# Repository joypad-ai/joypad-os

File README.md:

# Joypad OS

<p align="center">
  <picture>
    <source media="(prefers-color-scheme: dark)" srcset="docs/images/logo_solid.svg">
    <source media="(prefers-color-scheme: light)" srcset="docs/images/logo_solid_black.svg">
    
  </picture>
</p>
<p align="center">
  <strong>The Open-Source Firmware Platform for Game Controllers and Adapters</strong>
</p>
<p align="center">
  Build controller adapters, custom controllers, and assistive input devices — <br>on microcontrollers, not computers.
</p>
<p align="center">

</p>

---

## What is Joypad OS?

Joypad OS is firmware that runs on small microcontroller boards (RP2040, ESP32-S3, nRF52840) — the kind you'd find inside a controller or adapter, not on a PC. You flash it onto a chip and it handles everything: reading controllers, translating protocols, routing inputs to outputs, and managing button remapping.

**What you can build with it:**

- **Controller adapters** — Use any modern USB or Bluetooth controller on retro consoles (GameCube, Dreamcast, PCEngine, 3DO, and more) or convert retro controllers to USB
- **Custom controllers** — Wire up buttons, sticks, and sensors to a microcontroller and get a USB gamepad that works everywhere
- **Assistive gaming setups** — Merge multiple input devices (switches, joysticks, eye trackers) into a single controller output using flexible input routing
- **Wireless adapters** — Turn any Bluetooth controller into a wired USB gamepad for low-latency play

Under the hood, Joypad OS normalizes every input source into a common format, routes it through configurable player slots, and translates it into whatever output protocol the target needs — from retro console protocols bit-banged via PIO to modern USB HID and XInput.

Formerly known as **USBRetro**.

---

## I Have an Adapter — How Do I Update It?

1. **Download** the latest `.uf2` for your adapter from [Releases](https://github.com/joypad-ai/joypad-os/releases)
2. **Enter bootloader**: Hold BOOT + connect USB-C (or double-tap reset)
3. **Drag** the `.uf2` file onto the `RPI-RP2` drive that appears
4. **Done** — the drive ejects and your adapter is running the new firmware

**[Full installation guide](docs/getting-started/installation.md)** — troubleshooting, LED status codes, profile switching

---

## I Want to Build Something — Where Do I Start?

### Quick Start (RP2040)

```bash
# Install ARM toolchain (macOS)
brew install --cask gcc-arm-embedded cmake git

# Clone and initialize
git clone https://github.com/joypad-ai/joypad-os.git
cd joypad-os && make init

# Build an adapter
make usb2gc_kb2040     # USB/BT → GameCube
make usb2usb_feather   # USB/BT → USB HID
make bt2usb_pico_w     # Bluetooth → USB
make snes2usb_kb2040   # SNES controller → USB
```

### ESP32-S3

```bash
make init-esp                   # One-time ESP-IDF setup
make bt2usb_esp32s3             # Build
make flash-bt2usb_esp32s3       # Flash
```

### nRF52840

```bash
make init-nrf                               # One-time NCS setup
make bt2usb_seeed_xiao_nrf52840             # Build
make flash-bt2usb_seeed_xiao_nrf52840       # Flash
```

Output: `releases/joypad_os_<commit>_<app>_<board>.uf2`

**[Full build guide](docs/getting-started/building.md)** — prerequisites, all targets, ESP32/nRF setup, troubleshooting

---

## What Can It Do?

### Console Adapters

Use any USB or Bluetooth controller on retro consoles:

| Console | Apps | Highlights | Build | Docs |
|---------|------|-----------|-------|------|
| **PlayStation 4** | usb2usb | Local RSA auth, passthrough, rumble | [DIY](docs/hardware/diy.md) | [Guide](docs/architecture/ps4_auth.md) |
| **PCEngine / TurboGrafx-16** | usb2pce | Multitap (5 players), mouse, 2/3/6-button | [DIY](docs/hardware/diy.md) | [Guide](docs/apps/usb2pce.md) |
| **GameCube / Wii** | usb2gc, bt2gc | Profiles, rumble, keyboard mode | [Build](docs/hardware/builds/usb2gc.md) | [Guide](docs/apps/usb2gc.md) |
| **Sega Dreamcast** | usb2dc | Rumble, analog triggers, 4 players | [DIY](docs/hardware/diy.md) | [Guide](docs/apps/usb2dc.md) |
| **N64** | bt2n64 | Rumble pak emulation, profiles, BT | [DIY](docs/hardware/diy.md) | [Guide](docs/apps/bt2n64.md) |
| **Nuon DVD Players** | usb2nuon, bt2nuon | Controller, spinner (Tempest 3000), IGR | [DIY](docs/hardware/diy.md) | [Guide](docs/apps/usb2nuon.md) |
| **3DO Interactive Multiplayer** | usb23do | 8 players, mouse, extension passthrough | [DIY](docs/hardware/diy.md) | [Guide](docs/apps/usb23do.md) |
| **Neo Geo / SuperGun** | usb2neogeo | 7 profiles, 1L6B arcade layouts | [DIY](docs/hardware/diy.md) | [Guide](docs/apps/usb2neogeo.md) |
| **Casio Loopy** | usb2loopy | 4 players (experimental) | [DIY](docs/hardware/diy.md) | [Guide](docs/apps/usb2loopy.md) |

### USB & Wireless Adapters

| Adapter | What It Does | Platforms | Build | Docs |
|---------|-------------|-----------|-------|------|
| **USB2USB** | USB/BT controller → USB gamepad (XInput, PS3/4, Switch, etc.) | RP2040, nRF52840 | [DIY](docs/hardware/diy.md) | [Guide](docs/apps/usb2usb.md) |
| **BT2USB** | Bluetooth controller → wired USB gamepad | Pico W, ESP32-S3, nRF52840 | [Pico W](docs/hardware/builds/bt2usb-pico-w.md) | [Guide](docs/apps/bt2usb.md) |
| **WiFi2USB** | WiFi controller (JOCP) → USB gamepad | Pico W | [DIY](docs/hardware/diy.md) | [Guide](docs/apps/wifi2usb.md) |

### Native Controller Adapters

Convert retro controllers to USB or bridge them to other consoles:

| Adapter | From → To | Build | Docs |
|---------|----------|-------|------|
| **SNES2USB** | SNES/NES → USB | [KB2040](docs/hardware/builds/snes2usb-kb2040.md) | [Guide](docs/apps/snes2usb.md) |
| **NES2USB** | NES → USB | [DIY](docs/hardware/diy.md) | [Guide](docs/apps/nes2usb.md) |
| **N642USB** | N64 → USB | [DIY](docs/hardware/diy.md) | [Guide](docs/apps/n642usb.md) |
| **GC2USB** | GameCube → USB | [DIY](docs/hardware/diy.md) | [Guide](docs/apps/gc2usb.md) |
| **NEOGEO2USB** | Neo Geo arcade stick → USB | [DIY](docs/hardware/diy.md) | [Guide](docs/apps/neogeo2usb.md) |
| **LodgeNet2USB** | LodgeNet hotel controllers → USB | [Pico](docs/hardware/builds/lodgenet2usb-pico.md) | [Guide](docs/apps/lodgenet2usb.md) |
| **N642DC** | N64 → Dreamcast | [KB2040](docs/hardware/builds/n642dc-kb2040.md) | [Guide](docs/apps/n642dc.md) |
| **N642Nuon** | N64 → Nuon | [DIY](docs/hardware/diy.md) | [Guide](docs/apps/n642nuon.md) |
| **SNES23DO** | SNES → 3DO | [DIY](docs/hardware/diy.md) | [Guide](docs/apps/snes23do.md) |
| **LodgeNet2N64** | LodgeNet → N64 | [DIY](docs/hardware/diy.md) | [Guide](docs/apps/lodgenet2n64.md) |
| **LodgeNet2GC** | LodgeNet → GameCube | [DIY](docs/hardware/diy.md) | [Guide](docs/apps/lodgenet2gc.md) |

### Custom Controllers

Wire up GPIO buttons and analog sticks to build your own USB gamepad:

```bash
make controller_fisherprice_v1_kb2040  # Digital buttons → USB HID
make controller_fisherprice_v2_kb2040  # Buttons + analog stick → USB HID
make controller_macropad               # Adafruit MacroPad → USB HID
make universal_pico_w           # GPIO+JoyWing → BLE+USB HID (Pico W)
make universal_rp2040_abb       # GPIO+USB Host → USB HID (ABB Passthrough)
```

---

## Supported Input Devices

- **Xbox** — OG, 360, One, Series X|S (USB + Bluetooth)
- **PlayStation** — Classic, DS3, DS4, DualSense (USB + Bluetooth)
- **Nintendo** — Switch Pro, Switch 2 Pro, Joy-Con, NSO GameCube, GameCube adapter (USB + Bluetooth)
- **8BitDo** — PCE 2.4g, M30, NeoGeo, BT adapters
- **Other** — Hori, Logitech, Google Stadia, Sega Astro City, generic HID
- **Peripherals** — USB keyboards, mice, hubs, Bluetooth dongles
- **Native** — SNES, N64, GameCube, Neo Geo, LodgeNet hotel controllers (directly wired)

**[Full controller compatibility list](docs/hardware/controllers.md)**

---

## How It Works

```
Any Input                        Router                       Any Output
─────────                        ──────                       ──────────
USB controllers ──┐                                           ┌──→ Retro consoles
Bluetooth ────────┤                                           ├──→ USB gamepad
WiFi ─────────────┼──→  normalize  →  route  →  translate  ──┼──→ XInput / PS4 / Switch
SNES / N64 / GC ──┤         ↓                                ├──→ Keyboard + mouse
GPIO buttons ─────┘    profile_apply()                        └──→ Custom outputs
                    (button remapping)
```

- **Router** — SIMPLE (1:1), MERGE (all→one), or BROADCAST (all→all) modes
- **Profiles** — Per-app button remapping, cycled via SELECT + D-pad
- **Dual-Core** — Core 0 handles input, Core 1 handles timing-critical output (RP2040)
- **PIO** — Programmable I/O for console protocols (GameCube joybus, Dreamcast maple, etc.)

**[Architecture overview](docs/overview/architecture.md)** | **[Data flow](docs/overview/data-flow.md)**

---

## Platforms

| Platform | Chip | What Runs On It | Bluetooth | Build System |
|----------|------|----------------|-----------|--------------|
| **RP2040** | ARM Cortex-M0+ (dual-core) | All console adapters, USB output, custom controllers | Classic BT + BLE (Pico W) or via dongle | pico-sdk |
| **ESP32-S3** | Xtensa LX7 (dual-core) | bt2usb | BLE only | ESP-IDF |
| **nRF52840** | ARM Cortex-M4 | bt2usb, usb2usb | BLE only | nRF Connect SDK |

---

## Documentation

| Section | What's There |
|---------|-------------|
| **[Installation Guide](docs/getting-started/installation.md)** | Flashing firmware, troubleshooting, LED codes |
| **[Build Guide](docs/getting-started/building.md)** | Dev setup for macOS/Linux/Windows, all build targets |
| **[Supported Controllers](docs/hardware/controllers.md)** | USB, Bluetooth, keyboards, mice, dongles |
| **[Supported Boards](docs/hardware/boards.md)** | RP2040, ESP32-S3, nRF52840 board comparison |
| **[Wiring Guide](docs/hardware/wiring.md)** | USB host port + console connector pinouts |
| **[DIY Builds](docs/hardware/diy.md)** | Build your own, where to buy parts |
| **[ESP32-S3](docs/platforms/esp32.md)** | ESP-IDF setup, TinyUF2, architecture |
| **[nRF52840](docs/platforms/nrf52840.md)** | nRF Connect SDK setup, debugging |
| **[Architecture](docs/overview/architecture.md)** | How it works — data flow, router, I/O layers |
| **[Data Flow](docs/overview/data-flow.md)** | Input-to-output pipeline walkthrough |
| **[Protocol Reference](docs/protocols/3DO_PBUS.md)** | 3DO PBus, GameCube Joybus, Nuon Polyface, PCEngine |

---

## Community & Support

- **Discord**: [community.joypad.ai](http://community.joypad.ai/) - Community chat
- **Issues**: [GitHub Issues](https://github.com/joypad-ai/joypad-os/issues) - Bug reports
- **Email**: support@controlleradapter.com - Product support

---

## Acknowledgements

- [Ha Thach](https://github.com/hathach/) - [TinyUSB](https://github.com/hathach/tinyusb)
- [David Shadoff](https://github.com/dshadoff) - [PCEMouse](https://github.com/dshadoff/PC_Engine_RP2040_Projects/tree/main/PCEMouse) foundation
- [FCare](https://github.com/FCare) - [USBTo3DO](https://github.com/FCare/USBTo3DO) 3DO protocol implementation
- [mackieks](https://github.com/mackieks) - [MaplePad](https://github.com/mackieks/MaplePad) Dreamcast Maple Bus implementation
- [Ryzee119](https://github.com/Ryzee119) - [tusb_xinput](https://github.com/Ryzee119/tusb_xinput/)
- [SelvinPL](https://github.com/SelvinPL/) - [lufa-hid-parser](https://gist.github.com/SelvinPL/99fd9af4566e759b6553e912b6a163f9)
- [JonnyHaystack](https://github.com/JonnyHaystack/) - [joybus-pio](https://github.com/JonnyHaystack/joybus-pio)
- [OpenStickCommunity](https://github.com/OpenStickCommunity) - [GP2040-CE](https://github.com/OpenStickCommunity/GP2040-CE) USB device output modes

---

## License

Joypad OS is licensed under the **Apache-2.0 License**.

The **Joypad** name and branding are trademarks of Joypad Inc.

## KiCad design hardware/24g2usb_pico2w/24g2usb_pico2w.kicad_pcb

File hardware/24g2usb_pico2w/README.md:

# 24g2usb_pico2w carrier

Minimal carrier PCB for the [24g2usb](../../docs/apps/24g2usb.md) app on a Raspberry Pi Pico 2 W
(or Pico / Pico W / Pico 2 -- mechanically identical): holds an nRF24L01+ mini SMD module and
receives the Pico on two female header sockets covering only the pins actually needed. Board:
21 x 33mm (the Pico's own width, as short as the used pin span allows), 2-layer, 1.6mm FR4, 1oz
copper.

> **Not yet fabricated or tested, and the less settled of the two carriers.** This board is
> DRC-clean and its netlist is asserted against the firmware's wiring table, but nothing has been
> built from these files. Specific to this variant: the module's antenna overhangs the same board
> edge the Pico's USB-C connector occupies, and that clearance has only been checked in the 3D
> render, not against a real cable -- verify it with your own cable on the fit-check print. The
> [RP2350-Zero carrier](../24g2usb_rp2350zero/README.md) overhangs away from its USB end and is
> the better-understood board of the two.

Generated from [`../generate.py`](../generate.py) (`--variant pico2w`) -- same generator, same
module footprint, and the same routing method as the RP2350-Zero carrier; see that file's
docstring and the sibling [`24g2usb_rp2350zero/README.md`](../24g2usb_rp2350zero/README.md) for
the shared background. This README covers only what's specific to this board.

**No KiCad GUI step is required before ordering.** `make gerbers zip` produces a gerber/drill zip
ready to upload as-is -- see "Ordering" below.

## Why it's this shape

Only 16 of the Pico's 40 pins are used: pins 1-11 (GP0-GP8 plus two GND, all six SPI/IRQ
signals live in here) on J1, and pins 36-40 (3V3(OUT), 3V3_EN, GND, VSYS, VBUS -- only 3V3 and
the second GND are actually wired) on J3, purely to reach 3V3 and add a second mounting/support
point at the same end of the board. Both spans sit at the USB end of the Pico, so the carrier
only needs to be as tall as that span -- the rest of the Pico (about 21mm) cantilevers out past
the carrier's far edge, supported only by the header pins at this end.

The module sits in the ~13mm channel between J1 and J3, its antenna overhanging the carrier's
**USB-end edge**, in the same free-air gap the Pico's own USB-C connector needs anyway -- check
this against your actual connector and cable in the fit-check step below; it's the one clearance
this design can't verify for you from a render. C1/C2 (decoupling) sit in the same channel, south
of the module's pad-label text, between J1's CE row and the antenna keepout.

## Mounting orientation -- read before soldering anything

Same convention as the RP2350-Zero carrier, and the same warning applies: the Pico plugs in from
**above** (female sockets on the carrier's top face) or the carrier plugs into the Pico from
**below** (male headers soldered pointing down out of the carrier's bottom face, into a Pico
fitted with sockets) -- **never flip the carrier over to mate it**, or J1/J3's asymmetric pinouts
swap and 3V3 ends up across the SPI lines. "USB END" and each socket's pin-1 marker are present on
both the top and bottom face, so either mounting direction is unambiguous without holding the
board up to a light. Through-hole pads are on `*.Cu` and `*.Mask` on both sides -- a socket or a
header solders cleanly from either face, and nothing sits on the bottom face to obstruct a header
soldered from underneath.

## BOM

See [`fab/bom.csv`](fab/bom.csv).

| Ref | Part | Notes |
|-----|------|-------|
| U1 | nRF24L01+ "Mini SMD" module, 1.27mm pitch, 12x18mm body | Hand-solder -- JLCPCB stocks none of these |
| J1 | 1x11 2.54mm female header | Cut from a standard break-away strip |
| J3 | 1x5 2.54mm female header | Cut from a standard break-away strip |
| C1 | 10uF 0805 | Bulk decoupling, at U1's VCC/GND pads |
| C2 | 100nF 0805 | HF decoupling, at U1's VCC/GND pads |

No Pico 2 W on the BOM -- it's a separate board, plugged into J1/J3.

## Fab order settings (JLCPCB or similar)

- 2 layers, 1.6mm thickness, 1oz copper -- same as the RP2350-Zero carrier
- Min track/space 0.3mm/0.2mm (signal), 0.9mm GND
- Upload `fab/24g2usb_pico2w-gerbers.zip`
- Bare PCB order -- U1 is hand-soldered, not JLCPCB-assembled

## Ordering

1. `make -C hardware/24g2usb_pico2w all` (or `generate drc gerbers zip render` individually)
   regenerates the board, checks it, and produces everything in `fab/` -- no GUI step needed.
2. Print `fab/24g2usb_pico2w-top-1to1.pdf` at 100% scale (turn off "fit to page" in your PDF
   viewer) and lay your actual Pico 2 W and nRF24 module on it. The print includes the module's
   TRUE 12x18mm body (on the fabrication-reference layer, not silkscreen -- see the RP2350-Zero
   README's "Why the module outline isn't on silkscreen" for why). Check J1/J3's pad spacing
   against the Pico's own header holes, confirm the module is really a single row of 8 pads at
   1.27mm pitch, and -- specific to this board -- confirm the antenna overhang doesn't foul the
   USB-C cable you actually plan to use.
3. **Check the module's pad ORDER.** The board expects `+3.3V, GND, CE, CSN, SCK, MOSI, MISO,
   IRQ` along the row, VCC at the silkscreen-marked end. This is verified against the vendor
   dimension drawing for the common 12x18mm module (Sunrom model 3962,
   https://www.sunrom.com/p/rf-module-2-4ghz-nrf24l01-smd -- 12x18mm, 1.27mm pitch, first pad
   1.6mm from the edge), which is what this footprint was built from. These modules are NOT
   standardised between sellers, though, and carry no silkscreen on the pad row, so if yours came
   from elsewhere, probe for continuity between each pad and any bare ground on the module
   (crystal can, or the ground fill around the antenna): exactly one pad should beep, and it must
   be the second from the +3.3V end. If GND appears at the far end of the row instead, that module
   needs a different footprint. A swapped VCC/GND kills the module on first power-up.
4. Upload `fab/24g2usb_pico2w-gerbers.zip` to your fab of choice as a bare (non-assembled) 2-layer
   board.

## Assembly order

1. **Module first** (U1) -- tack one corner, check against the fit-check print, then finish
   soldering.
2. **C1, C2** -- right next to U1's VCC/GND pads.
3. **J1 and J3 sockets** (or headers, if mounting the carrier above the Pico) -- last, since
   they're the tallest parts.
4. Plug in the Pico 2 W (with headers fitted, if the carrier has sockets).

## 3V3, not 5V

VCC is fed from the Pico's 3V3(OUT) pin (J3 pin 36), never VBUS/VSYS -- called out on the
silkscreen next to the module.

## Verification performed

- `kicad-cli pcb drc --severity-all --exit-code-violations`: **0 violations, 0 unconnected items,
  0 schematic-parity issues.**
- Netlist assertion in `generate.py` passes: J1+J3 (merged) and U1's pad-to-net mapping checked
  against the wiring table before any file is written.
- Renders and the 1:1 PDF inspected: pads on the expected nets, nothing routed under the antenna's
  strict keepout, module correctly centred in the channel between J1 and J3, C1/C2 right next to
  U1's VCC/GND pads, bottom face clean. The module's antenna overhangs the board edge by about
  6.75mm with no copper anywhere under it, confirmed both from the F.Fab outline in the 1:1 print
  and from the (automatically DRC-checked) antenna keepout zone.
- Gerber round-trip: unzipped `fab/24g2usb_pico2w-gerbers.zip` and confirmed F.Cu, B.Cu,
  F.Silkscreen, B.Silkscreen, F.Mask, B.Mask, Edge.Cuts, the Excellon drill file, and the job file
  are all present, and that F.Cu/B.Cu actually contain the designed copper (0.3mm signal traces,
  0.9mm GND traces, and the SMD/THT pad apertures) rather than an empty or pour-only layer.

## Known limitations

- **Ground is carried by explicit 0.9mm-wide tracks, not a copper pour** -- same reasoning as the
  RP2350-Zero carrier: `kicad-cli`'s headless zone filler segfaults in this Docker toolchain, so a
  pour would ship silently unfilled in the gerbers. An explicit track sidesteps the problem
  entirely.
- **Silkscreen labels are tight.** J1's pin labels (GP0..GP8, GND) and J3's (abbreviated to
  VB/VS/GN/EN/3V to fit the 2.54mm pitch rotated vertical) sit close to their own pin. Full pin
  names are in the BOM and the table above -- read the silkscreen with this file open if a label
  is ambiguous.
- **Antenna/cable clearance** is the one physical check this design leans on you for -- see the
  fit-check step.

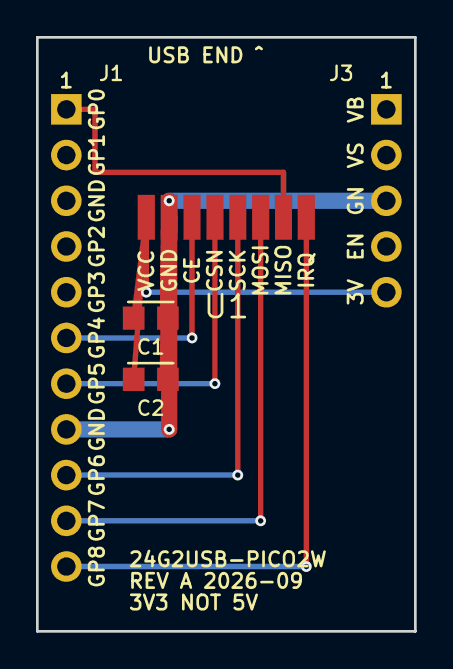
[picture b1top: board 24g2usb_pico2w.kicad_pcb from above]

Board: 2 copper layers, 21.0 x 33.0 mm, 5 parts (0 on the bottom side), 8 nets.

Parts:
C1: 10uF; C_0805_Hand
C2: 100nF; C_0805_Hand
J1: Pico_Socket_1x11
J3: Pico_Socket_1x5
U1: nRF24L01_Mini_SMD_8P127

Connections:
3V3: C1.1, C2.1, J3.5, U1.1
GND: C1.2, C2.2, J1.8, J3.3, U1.2
GP0_MISO: J1.1, U1.7
GP4_CE: J1.6, U1.3
GP5_CSN: J1.7, U1.4
GP6_SCK: J1.9, U1.5
GP7_MOSI: J1.10, U1.6
GP8_IRQ: J1.11, U1.8

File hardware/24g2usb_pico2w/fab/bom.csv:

Reference,Qty,Value,Footprint,Description,Notes
J1,1,Pico_Socket_1x11,hand-wound 1x11 2.54mm socket,"Female header socket, 1x11, 2.54mm pitch",Cut from a standard break-away strip
J3,1,Pico_Socket_1x5,hand-wound 1x5 2.54mm socket,"Female header socket, 1x5, 2.54mm pitch",Cut from a standard break-away strip
U1,1,nRF24L01_Mini_SMD_8P127,"nRF24L01+ mini SMD module, 1.27mm pitch","2.4GHz transceiver module, single-row castellated SMD",Hand-solder; JLCPCB does not stock this part
C1,1,C_0805_Hand,10uF 0805 X5R/X7R,"Bulk decoupling, at U1's VCC/GND pads",
C2,1,C_0805_Hand,100nF 0805 X7R,"HF decoupling, at U1's VCC/GND pads",

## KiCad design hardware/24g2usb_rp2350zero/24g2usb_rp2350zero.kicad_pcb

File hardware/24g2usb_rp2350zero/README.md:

# 24g2usb_rp2350zero carrier

Carrier PCB for the [24g2usb](../../docs/apps/24g2usb.md) app: holds an nRF24L01+ mini SMD
module and receives a Waveshare RP2350-Zero on female header sockets. Board: 18.5 x 26.0mm
(the Zero's own footprint, plus a comfortable margin), 2-layer, 1.6mm FR4, 1oz copper.

> **Not yet fabricated or tested.** This board is DRC-clean and its netlist is asserted against
> the firmware's wiring table, but no physical board has been built from these files. Treat it as
> a first spin: do the fit-check print and the module pad-order check below before ordering.

Everything here is generated from [`../generate.py`](../generate.py) (`--variant rp2350zero`) --
edit the tables in that file and regenerate rather than hand-editing the `.kicad_pcb`. See its
module docstring for the routing method and why it looks the way it does.

**No KiCad GUI step is required before ordering.** `make gerbers zip` produces a gerber/drill zip
ready to upload as-is -- see "Ordering" below.

## Mounting orientation -- read before soldering anything

The RP2350-Zero plugs in from **above**: female sockets soldered to this carrier's **top** face,
Zero's male header pins pointing down into them. The carrier can also go **above** the Zero
instead -- solder male header pins into J1 pointing down out of the carrier's **bottom** face,
and plug those into a Zero that has female sockets fitted. Both ways put the module's antenna on
the carrier's top face; mounting the carrier above additionally gives the antenna clear air above
it with nothing overhead.

**Never flip the board over to mate it.** J1's two columns are not left-right symmetric (5V/GND/
3V3/GPxx on one side, GP0-GP8 on the other) -- mating flipped swaps them and puts 3V3 across the
SPI lines. Both faces are marked for this: "USB-C END" and the pin-1 marker (a square pad) are
present on **both** the top and bottom face, so whichever face you solder a header to, orientation
is never a guess. Through-hole pads are on `*.Cu` and `*.Mask` (both sides), so a socket or a
header solders cleanly from either face.

## BOM

See [`fab/bom.csv`](fab/bom.csv). Headline parts:

| Ref | Part | Notes |
|-----|------|-------|
| U1 | nRF24L01+ "Mini SMD" module, 1.27mm pitch, 12x18mm body | Hand-solder -- JLCPCB stocks none of these |
| J1 | 2x9 2.54mm female header, 15.24mm row spacing | Cut two 1x9 strips, or one 2x9 if you have it |
| C1 | 10uF 0805 | Bulk decoupling, right at the module's VCC/GND pads |
| C2 | 100nF 0805 | HF decoupling, right at the module's VCC/GND pads |

No RP2350-Zero on the BOM -- it's a separate board you already have, plugged into J1. This board
has no breakout header for the Zero's unused pins and no mounting holes -- see "Known
limitations."

## Fab order settings (JLCPCB or similar)

- 2 layers, 1.6mm thickness, 1oz copper, green soldermask, white silkscreen (defaults are fine)
- Min track/space 0.3mm/0.2mm (signal), 0.9mm GND -- inside every fab's standard capability
- Upload `fab/24g2usb_rp2350zero-gerbers.zip` (Gerber + Excellon drill, RS-274X)
- **This is a bare PCB order.** JLCPCB has no nRF24 module in its assembly catalogue -- do not
  select PCBA/assembly for U1

## Ordering

1. `make -C hardware/24g2usb_rp2350zero all` (or `generate drc gerbers zip render` individually)
   regenerates the board, checks it, and produces everything in `fab/` -- no GUI step needed.
2. Print `fab/24g2usb_rp2350zero-top-1to1.pdf` at 100% scale (**disable "fit to page" / "scale to
   fit" in your PDF viewer's print dialog**) and lay your actual RP2350-Zero and nRF24 module on
   it -- the one check the software genuinely can't do for you. The print includes the module's
   TRUE 12x18mm body (on the fabrication-reference layer, not silkscreen -- see "Why the module
   outline isn't on silkscreen" below), including the antenna overhang past the board edge.
   Confirm J1's pad spacing matches the Zero's header pins, and that the module you have is really
   a single row of 8 pads at 1.27mm pitch -- seller listings for "mini nRF24L01+ SMD" modules
   aren't fully standardized, and this is the one mistake DRC can't catch.
3. **Check the module's pad ORDER.** The board expects `+3.3V, GND, CE, CSN, SCK, MOSI, MISO,
   IRQ` along the row, VCC at the silkscreen-marked end. This is verified against the vendor
   dimension drawing for the common 12x18mm module (Sunrom model 3962,
   https://www.sunrom.com/p/rf-module-2-4ghz-nrf24l01-smd -- 12x18mm, 1.27mm pitch, first pad
   1.6mm from the edge), which is what this footprint was built from. These modules are NOT
   standardised between sellers, though, and carry no silkscreen on the pad row, so if yours came
   from elsewhere, probe for continuity between each pad and any bare ground on the module
   (crystal can, or the ground fill around the antenna): exactly one pad should beep, and it must
   be the second from the +3.3V end. If GND appears at the far end of the row instead, that module
   needs a different footprint. A swapped VCC/GND kills the module on first power-up.
4. Upload `fab/24g2usb_rp2350zero-gerbers.zip` to your fab of choice as a bare (non-assembled)
   2-layer board.

## Assembly order

1. **Module first** (U1) -- hardest part to align, easiest to rework before anything else is in
   the way. Tack one corner pad, check alignment against the printed fit-check, then solder the
   rest.
2. **C1, C2** -- right next to U1's VCC/GND pads.
3. **J1 socket** -- last, since it's the tallest part and the easiest to bump while soldering the
   others.
4. Solder male headers to your RP2350-Zero (if not already fitted) and plug it into J1.

## 3V3, not 5V

The module's VCC pad is fed from the Zero's 3V3 pin, never 5V -- nRF24 modules are not 5V
tolerant on their supply. This is called out on the silkscreen next to the module. If you're
hand-wiring anything extra, don't cross it.

## Why the module outline isn't on silkscreen

The nRF24 module's antenna genuinely overhangs the board edge on this carrier (by design -- see
"Verification performed" below for the exact figure) with no copper underneath it. A full-length
silkscreen outline of the module's true 12x18mm body would have to cross Edge.Cuts to show that
overhang, and KiCad's DRC flags silk that crosses the board edge (`silk_edge_clearance`). Rather
than ship that DRC note, the true body outline is drawn on `F.Fab` instead -- a fabrication
reference layer, not printed ink, so it isn't DRC-constrained against the edge -- and the
Makefile's 1:1 PDF/SVG exports include `F.Fab` specifically so the antenna overhang is still
visible and checkable when you print it. Silkscreen itself just carries the pad labels, reference
designators, and orientation markers; the pad copper marks the module's row on the physical board.

## Verification performed

- `kicad-cli pcb drc --severity-all --exit-code-violations`: **0 violations, 0 unconnected items,
  0 schematic-parity issues.**
- Netlist assertion in `generate.py` passes: J1 and U1's pad-to-net mapping is checked against the
  wiring table from `docs/apps/24g2usb.md` / `rf24g_host.h` before any file is written.
- Renders (`fab/*.png`, `fab/*.svg`) and the 1:1 PDF inspected: pads land on the expected nets,
  nothing routed under the module's antenna keepout, silkscreen legible, C1/C2 sit right next to
  U1's VCC/GND pads, board outline a plain rectangle, bottom face clean (no components, nothing
  obstructing the header holes). The module's antenna overhangs the board edge by about 7.75mm
  with no copper anywhere under it, confirmed both from the F.Fab outline in the 1:1 print and
  from the (automatically DRC-checked) antenna keepout zone.
- Gerber round-trip: unzipped `fab/24g2usb_rp2350zero-gerbers.zip` and confirmed F.Cu, B.Cu,
  F.Silkscreen, B.Silkscreen, F.Mask, B.Mask, Edge.Cuts, the Excellon drill file, and the job file
  are all present, and that F.Cu/B.Cu actually contain the designed copper (0.3mm signal traces,
  0.9mm GND traces, and the SMD/THT pad apertures) rather than an empty or pour-only layer.

## Known limitations

- **No GPIO breakout header and no M2 mounting holes.** An earlier revision of this board planned
  both, but at 18.5mm wide there wasn't room for either without conflicting with J1's own pads or
  routing -- see `generate.py`'s comments near `J1_POS`/mounting-hole for the specific numbers.
  The board relies on J1's own socket for mechanical support.
- **Ground is carried by explicit 0.9mm-wide tracks, not a copper pour.** `kicad-cli`'s headless
  zone filler segfaults in this Docker toolchain even for a single trivial zone (confirmed, not
  assumed), so a pour would ship silently unfilled in the gerbers -- what the fab builds wouldn't
  match the design. Routing GND as an explicit track sidesteps the problem entirely rather than
  requiring a manual GUI fill-and-reexport step before every order.

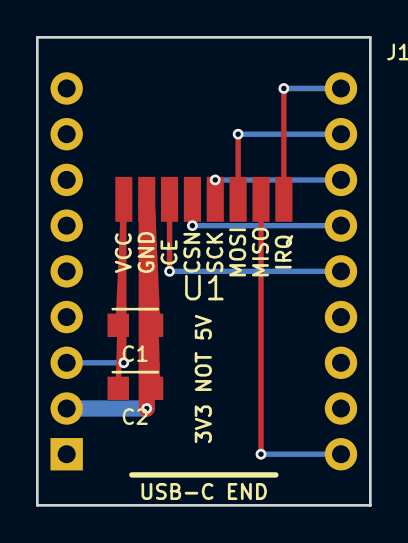
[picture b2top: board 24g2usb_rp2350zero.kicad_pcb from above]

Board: 2 copper layers, 18.5 x 26.0 mm, 4 parts (0 on the bottom side), 8 nets.

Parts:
C1: 10uF; C_0805_Hand
C2: 100nF; C_0805_Hand
J1: RP2350-Zero_Socket
U1: nRF24L01_Mini_SMD_8P127

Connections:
3V3: C1.1, C2.1, J1.3, U1.1
GND: C1.2, C2.2, J1.2, U1.2
GP0_MISO: J1.10, U1.7
GP4_CE: J1.14, U1.3
GP5_CSN: J1.15, U1.4
GP6_SCK: J1.16, U1.5
GP7_MOSI: J1.17, U1.6
GP8_IRQ: J1.18, U1.8

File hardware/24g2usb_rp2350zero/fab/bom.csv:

Reference,Qty,Value,Footprint,Description,Notes
J1,1,RP2350-Zero_Socket,hand-wound 2x9 2.54mm socket,"Female header socket, 2x9, 2.54mm pitch (e.g. two 1x9 strips)",Not on LCSC as one part -- use generic 2.54mm female header strip
U1,1,nRF24L01_Mini_SMD_8P127,"nRF24L01+ mini SMD module, 1.27mm pitch","2.4GHz transceiver module, single-row castellated SMD",Hand-solder; JLCPCB does not stock this part
C1,1,C_0805_Hand,10uF 0805 X5R/X7R,"Bulk decoupling, at U1's VCC/GND pads",
C2,1,C_0805_Hand,100nF 0805 X7R,"HF decoupling, at U1's VCC/GND pads",

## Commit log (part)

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2026-05-03 joypad-mcp: camera pause/resume, joypad connect UI, ffmpeg orphan sweep
    Three quality-of-life improvements after long session usage:
    - Camera pause/resume button in the web UI (POST /api/camera/pause and
    /resume). Releases the camera device so the iPhone Continuity Camera
    indicator clears when the assistant isn't actively using it. Frame
    polling auto-pauses too — no more 503 spam in the network tab.
    - ffmpeg orphan sweep at MCP boot and before every camera start. SIGTERM
2026-05-05 Makefile: route gc2usb_pico to its own CMake target (GP28)
    `make gc2usb_pico` was building joypad_gc2usb (the KB2040 CMake target,
    GC_PIN_DATA=29) with the Pico board script. Pico's GP29 isn't broken
    out — it's wired internally to VSYS for ADC battery monitoring — so the
    firmware was driving joybus traffic onto an inaccessible pin while
    users wired controllers to GP28 expecting it to work. Multiple users
    reported gc2usb_pico failing for this reason.
2026-05-05 joypad-mcp: web UI UART log panel + tolerate port-in-use
    - New /api/joypad/log endpoint returns recent lines from the adapter's
    UART ring buffer with optional regex filter (since_ms=60000 default).
    - ui.html grows a "UART log" panel: live tail @ 500ms, regex grep,
    pause/resume, clear button. De-dupes by (index, line) so periodic
    status prints don't double-tail. Trims panel to last 200 lines so
    long sessions don't blow up the DOM.
2026-05-06 player_leds_gpio: 4-LED player indicator on raw GPIOs (compile-time, opt-in)
    Drive 4 GPIO pins from the same 4-bit PLAYER_LEDS[] bitmap that PS3,
    Switch Pro, and SInput controllers already use internally — so a custom
    controller_btusb build wired with through-hole player LEDs lights up
    P1..P4 (and combo patterns for P5..P10) at a glance. Active-high to
    match BOARD_LED_PIN convention.
    Compile-time-only feature, off by default. Hooks in controller_btusb
2026-05-30 libjoypad: establish src/lib/libjoypad/ + move contract headers
    First step toward extracting joypad-os USB/BT controller parsing into a
    portable C library consumable by firmware, joypad-web (WASM), and
    joypad-unreal (UE5 plugin). See .dev/docs/libjoypad.md.
    Scaffolds the libjoypad directory and moves input_event.h and buttons.h
    to src/lib/libjoypad/include/joypad/. Old paths in src/core/ become
    one-line forwarders so the ~100 firmware files that include them keep
2026-05-30 libjoypad: add minimal-c example (HIDAPI + libjoypad on host)
    Phase 6 of the libjoypad extraction — smallest possible consumer.
    Plain ANSI C + HIDAPI command-line tool:
    - Enumerates HID devices via HIDAPI
    - Identifies DualSense / Victrix Pro PS5 via joypad_is_sony_ds5
    - Prints joypad_caps_t for the connected device
    - Sends a startup feedback report (gentle rumble + blue lightbar +
2026-05-30 libjoypad: link libjoypad sources into firmware builds
    The previous DS5 firmware-glue change introduced calls into libjoypad
    symbols (joypad_is_sony_ds5, joypad_parse_sony_ds5,
    joypad_build_sony_ds5_feedback) but the new libjoypad .c sources were
    not added to the firmware's translation-unit list. RP2040 link failed
    with undefined references.
    Add src/lib/libjoypad/src/devices/usb/hid/sony/ds5.c to:
2026-05-31 libjoypad: DS5 fixture replay harness + capture tool
    No physical DualSense visible from this workstation (only the KB2040
    serial bridge is plugged in), so this commit stages the
    infrastructure rather than the captures themselves. Real binary
    fixtures slot in as soon as a session with a connected DS5 runs the
    capture script.
    Three pieces:
2026-05-31 libjoypad: port Sony DualShock 3 / SIXAXIS USB driver
    Fifth driver migrated. DS3 is the outlier of the Sony USB family:
    pressure-sensitive D-pad, face, shoulder, and trigger buttons;
    single-axis (Z) gyro at ±100 dps; big-endian motion values
    centered at 512. No touchpad, no lightbar, no adaptive triggers.
    Exports:
    joypad_is_sony_ds3(vid, pid) — Sony VID 0x054c, PID 0x0268
2026-06-04 nes2usb: 4-player NES multitap support (#150)
    Extends nes2usb to support 4 simultaneous NES controllers via physical multitap wiring using 4-bit parallel PIO reads on consecutive DATA pins.
    Implements Phases 1-3 of the plan in docs/nes-multitap-plan.md:
    - PIO: in pins, 4 for parallel reads
    - Driver: per-port state, independent debounce/connection detection
    - Events: up to 4 input_event_t (dev_addr 0xF0-0xF3)
    - Dynamic get_device_count()
2026-06-16 feat: global analog-stick deadzone (single user-facing knob)
    Add one router-level deadzone applied to both sticks, above profiles, set
    over CDC via ROUTER.DEADZONE.SET (0-127, default 0 = off). Radial + scaled
    so center jitter is removed without losing full deflection or diagonal
    corners; triggers (L2/R2) untouched. Integer-only math (no sqrtf/-lm) since
    router.c compiles on all four platforms.
    - flash: uint8_t deadzone carved from reserved[] (256-byte layout unchanged,
2026-06-17 web-config: surface serial connect failures with an error toast
    On Chrome/Linux, port.open() can succeed even when serial access is blocked
    by permissions, leaving a dead port. The connect flow flipped the UI to
    "Connected" immediately, then loadAll()'s commands timed out — but
    device-info.load() swallows that timeout (logs only), so the UI sat on
    "connected" with no data and no indication anything was wrong.
    - Verify the device responds BEFORE showing connected: connectSerial/
2026-06-19 chore(version): single source of truth — derive everything from VERSION
    - Remove the per-app APP_VERSION manifest constant (44 stale, independently
    drifting copies); boot banners now print JOYPAD_VERSION (the repo VERSION file).
    - Derive USB bcdDevice from VERSION in the nRF and ESP builds too (was RP2040-
    only), so the MouthPad utility's "dongle version" reflects the firmware version
    on every platform.
    Net: VERSION drives the INFO command, the boot banner, and the USB bcdDevice
2026-06-22 fix(bt): per-connection BLE HID client — support two BLE HID devices
    Move hids_cid, the gatt setup sequencer (mp_hid_setup), and HID report routing
    off single globals into per-connection state, routing every hids_client event by
    its own cid. A single global cross-wired two devices' descriptors and dumped all
    reports onto the last-connected slot (garbage/haywire); the 1-client cap had
    hidden it for years. Bump MAX_NR_HIDS_CLIENTS/GATT_CLIENTS/BATTERY + descriptor
    storage for two devices. Also: recognize the MouthPad by DIS PnP VID/PID
2026-06-23 feat(pce2usb): native PCEngine controller -> USB HID adapter
    New app reading a real PCEngine/TurboGrafx-16 pad as a USB HID gamepad.
    - pce_host driver (native/host/pcengine): bit-bangs the 74157 mux directly
    at ~60Hz (no PIO needed — PCE pads have no clock to track). SEL high =
    d-pad, SEL low = I/II/Select/Run, all active-low.
    - Button mapping matches the PCE *device* interface (B2->I, B1->II) for
    round-trip consistency; d-pad/Select/Run unchanged.
2026-06-23 fix(bt): 8BitDo M30 digital L2/R2 remap — suppress phantom analog triggers
    The M30's shoulder buttons are digital, but its BT HID report also exposes
    them as Rx/Ry analog trigger axes. The generic BT gamepad driver mapped those
    to analog[L2/R2], which bypass button remapping (remap only touches the button
    bitmap), so users couldn't reassign L2/R2 — the trigger kept firing.
    Detect the M30 by VID/PID (0x2DC8 / 0x0651 over BT; its USB PID is 0x5006) and
    zero the analog L2/R2 so only the digital buttons drive output, keeping them
2026-06-23 fix(nrf): add mouthpad_ble.c to controller_btusb sources
    bthid_registry.c calls mouthpad_ble_register() unconditionally, but the
    controller_btusb nRF source list omitted mouthpad_ble.c (bt2usb/btusb2usb
    include it), causing an undefined-reference link failure in CI.
2026-06-24 fix(bt): match 8BitDo M30 by name (PID varies / unresolved across units)
    Some M30 units never resolve VID/PID over BT — matched only by BT class-of-
    device, so vendor_id/product_id stay 0 (web config shows "M30 gamepad (bt
    class)") — and others report different PIDs across firmware/mode. The PID-only
    match then misses them and the digital L2/R2 shoulders keep leaking analog
    trigger (L2:255), bypassing remap. Match primarily on the device name ("M30"),
    which is stable across variants; keep VID/PID as a secondary match.
2026-06-24 release: prep v2.2.0 — VERSION bump + changelog
    pce2usb (multitap + 6-button), mouthpad, CH32V307 platform, Xbox OG/One output
    fixes, M30 trigger remap, Dreamcast VMU QSPI storage, usb2dc RAM fix, tinyusb
    0.20.0-ch32 unification.
2026-06-24 feat(usb-hid): ELO Vagabond V1 button map (VID 0483/PID A4DB)
    The generic DInput reshuffle scrambled the ELO's buttons (A->Y, R2->Start,
    L1/R1 dead, etc.) because its HID button order doesn't match the typical
    DInput layout. Add a per-device direct HID-index -> JP_BUTTON override (NULL
    for all other devices, so their behavior is unchanged) and a map for the ELO:
    A/B/X/Y, L1/R1, L2/R2 (digital + the analog Sim-Controls triggers), Select/
    Start, and the back paddles -> JP_BUTTON_L4/R4.
2026-06-25 fix(bt2gc): detect console via dedicated GC_3V3_PIN, not joybus data-pin hack
    Read the GameCube's 3.3V rail on the dedicated sense GPIO (GC_3V3_PIN/GP6,
    previously defined but unused) instead of the usb2gc/wii2gc joybus data-pin
    pull-down trick. HIGH = console powered -> GameCube output; LOW (pull-down) =
    off-console -> USB output. Simpler and unambiguous (power presence, not a
    resistor divider against the console's signal pull-up).
2026-06-25 fix(dreamcast): make whole Core1 Maple path RAM-resident — eliminate save drops
    The no-TX-pause fix left occasional drops: the Core1 dispatch still called
    flash-resident libc/SDK functions on certain commands — memcpy on VMU block
    read/write and PuruPuru writes, memset on VMU writes, and time_us_32() on
    rumble. When one of those landed while Core0 had XIP disabled for a VMU/settings
    flash erase, Core1 stalled mid-poll and the DC dropped the controller. Rare
    because it needs the coincidence, but rumble + saves make it happen in play.
2026-06-25 fix(bt2gc): detect console off the data line, not the unused 3.3V sense pin
    bt2gc's USB-output fallback detected the GameCube by reading GC_3V3_PIN (GP6,
    the 3.43V rail). But GC_3V3_PIN was defined-but-unused before this app, so every
    GameCube-only board built for 2.1.0 was never wired to GP6 — it floats low, so
    bt2gc concluded "no console" and booted into USB output, breaking the GameCube
    output that worked in 2.1.0.
    Detect off GC_DATA_PIN (GP7) instead — the joybus signal line is always wired,
2026-06-29 fix(controller_btusb): free XIAO D1/P0.03 — disable colliding user button
    On the XIAO, button_nrf.c hardcodes the board "user button" to P0.03 (D1),
    the same GPIO used for a gamepad button via the pad config. Presses fed both
    the pad input (correct, e.g. B2) and the user-button driver, whose
    double-click cycles the USB output mode and triple-click resets to SInput —
    so wiring a button to D1 caused spurious mode changes.
    The XIAO has no dedicated user button, so add DISABLE_USER_BUTTON: when set,
2026-06-30 fix(xiao): enable gpio1 — P1.x pads (D6-D10) were dead
    The nRF52840 base devicetree leaves gpio1 (the entire P1 GPIO port)
    status="disabled", and the XIAO board never enables it. The XIAO breaks out
    D6-D10 = P1.11-P1.15 (pad pins 43-47), so any button/D-pad mapped to a P1.x pin
    silently did nothing: device_is_ready(gpio1) returns false, platform_gpio_nrf
    skips configuring the pin, and reads return garbage (floating) — which looked
    like the D-pad directions were swapped. P0.x pins worked because gpio0 is
2026-06-30 feat(sinput): report device's own battery + charge state in SInput report
    SInput already carries charge_level/plug_status, populated by sinput_mode from
    event->battery_level/battery_charging — but those only ever came from a
    connected INPUT controller (DS4/DS5 etc.). On controller_btusb the device IS
    the controller, so the fields stayed 0 and hosts saw no battery.
    Feed the device's own battery into the output event:
    - router: router_set_onboard_battery(percent, charging); the router stamps it
